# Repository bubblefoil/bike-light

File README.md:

# Cargo bike illumination

Cusomized bicycle RGB LED strip illumination controlled by Arduino UNO

# TODO
## Rezimy
- __Nocni:__ svitit vpredu max intenzitou (cca 6 LED z kraje), zbytek do konce nosice prichciple. To same v cervene vzadu.
- __Denni:__ To same co nocni, akorat ty prichciple nesviti vubec (stejne by to nebylo videt)
- __Parkovacky:__ sviti to prichciple cele, pricemz by bylo hezke umet menit intenzitu.
- __Blinkry:__ Max intenzivne oranzove z kraje prvnich cca 12LED prerusovane (oranzova/zhasnuto) a zbytek pri dennim nic a nocnim prichciple (bila ^ cervena)

## Rezimy 2.0

- __OFF:__ Vse 0%. Nejaka indikace?
- __Auto:__
  - Stred: 100%
  - Strany: Podle senzoru. Viz tabulka niz. Moznost menit citlivost stejne jako nastaveni jasu, tj. drzenim prepinace rezimu. Melo by stacit posouvat hranici sero/svetlo, kdy se strany vypinaji.
- __Manual:__
  - Vse podle hodnoty nastavene drzenim prepinace rezimu: 0-100%
  - 0-50%
    - Stred: 10-100%
    - Strany: Vypnute
  - 50-100%
    - Stred: 100%
    - Strany: 0-100%
- __Parking:__
  - Jas podle hodnoty nastavene drzenim prepinace rezimu: 0-100%
  - Vse sviti stejne
- __Usporny rezim:__
  - Jas podle hodnoty nastavene drzenim prepinace rezimu: 0-100%
  - Stred: Blikani (plynule pulzovani? Animace jednotlivych LED?)
  - Strany: Vypnute
  - Zmensit jas/sirku blinkru?

| Senzor    | Jas [%] |
| --------- | ------- |
| Tma       | ~1      |
| Sero      | ~25     |
| Svetlo    | 0       |

> To by bylo v prvni verzi vsechno. Couvacky, signalizace zamykani, kradeni, svetelna houkacka, vykreslovani bassu hudby apod.nechame na pozdeji ;)

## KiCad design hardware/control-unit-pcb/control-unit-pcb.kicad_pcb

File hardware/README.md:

# Controller HW diagram

The cargo bike is already equiped with its own 12V battery.

Controller is programmed to work with 3 switches. A couple for turn signals and one with press/hold functions to switch light modes and control brightness.
There are [motorcycle switches like this](https://www.banggood.com/22mm-Handlebar-Light-Horn-OnOff-Signal-Indicator-Switch-For-Motorcycle-E-bike-p-1211467.html) available on the market.

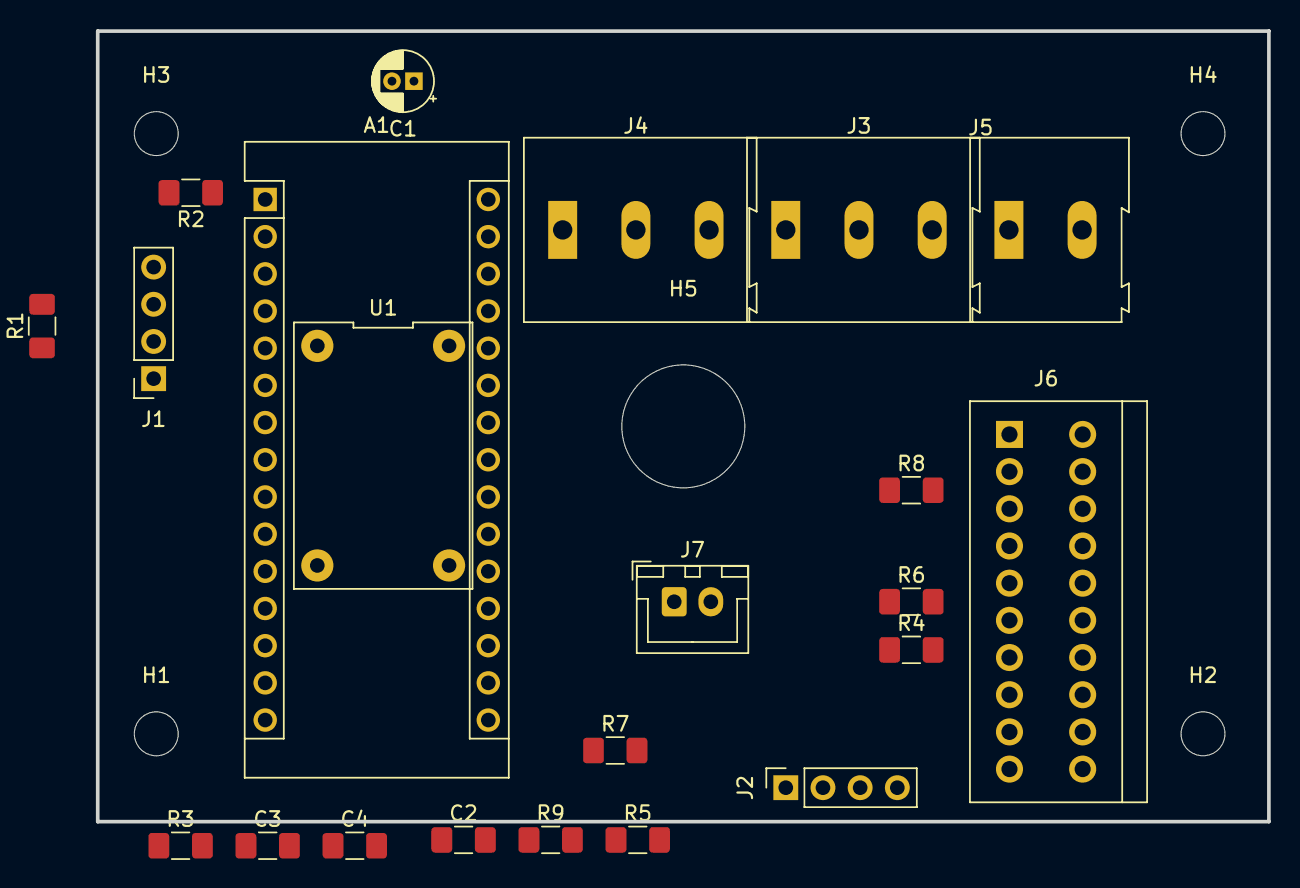
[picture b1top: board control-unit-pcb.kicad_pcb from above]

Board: 2 copper layers, 80.0 x 54.0 mm, 27 parts (0 on the bottom side), 15 nets, no tracks yet.

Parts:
A1: Arduino_Nano_v3.x; Arduino_Nano
C1: 1uF; CP_Radial_D4.0mm_P1.50mm
C2, C3, C4: 100nF; C_1206_3216Metric_Pad1.42x1.75mm_HandSolder
H1, H2, H3, H4: MountingHole; MountingHole_3mm
H5: MountingHole; MountingHole_8.4mm_M8
J1, J2: Conn_01x04_Male; PinSocket_1x04_P2.54mm_Vertical
J3, J4: Screw_Terminal_01x03; TerminalBlock_Altech_AK300-3_P5.00mm
J5: Screw_Terminal_01x02; TerminalBlock_Altech_AK300-2_P5.00mm
J6: Conn_02x10_Row_Letter_Last; TerminalBlock_PTR_AKZ3191_10KD-2x10_2.54x5.00
J7: Conn_01x02_Male; JST_XH_B2B-XH-A_1x02_P2.50mm_Vertical
R1: 2k2; R_1206_3216Metric_Pad1.42x1.75mm_HandSolder
R2: 1k2; R_1206_3216Metric_Pad1.42x1.75mm_HandSolder
R3, R4, R5, R6, R7: R; R_1206_3216Metric_Pad1.42x1.75mm_HandSolder
R8: 2M; R_1206_3216Metric_Pad1.42x1.75mm_HandSolder
R9: 10M; R_1206_3216Metric_Pad1.42x1.75mm_HandSolder
U1: MP2307; MP2037

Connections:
+5V: A1.27, J1.1, J7.2
+7.5V: A1.30, C1.1, C2.2
GND: A1.4, A1.29, C1.2, C2.1, C3.2, C4.2, J1.2, J2.4, J3.1, J4.3, J5.1, R1.1, R7.1, R8.1
LED_FL: J4.1, R6.2
LED_FR: J3.3, R5.2
unnamed: A1.1, R2.1
unnamed: A1.5, R3.1
unnamed: A1.6, R4.1
unnamed: A1.7, R5.1
unnamed: A1.8, R6.1
unnamed: A1.19, C3.1, J7.1, R7.2
unnamed: A1.20, C4.1, R8.2, R9.2
RX: A1.2, J1.3
TX: J1.4, R1.2, R2.2
VCC: J2.1, J3.2, J4.2, J5.2

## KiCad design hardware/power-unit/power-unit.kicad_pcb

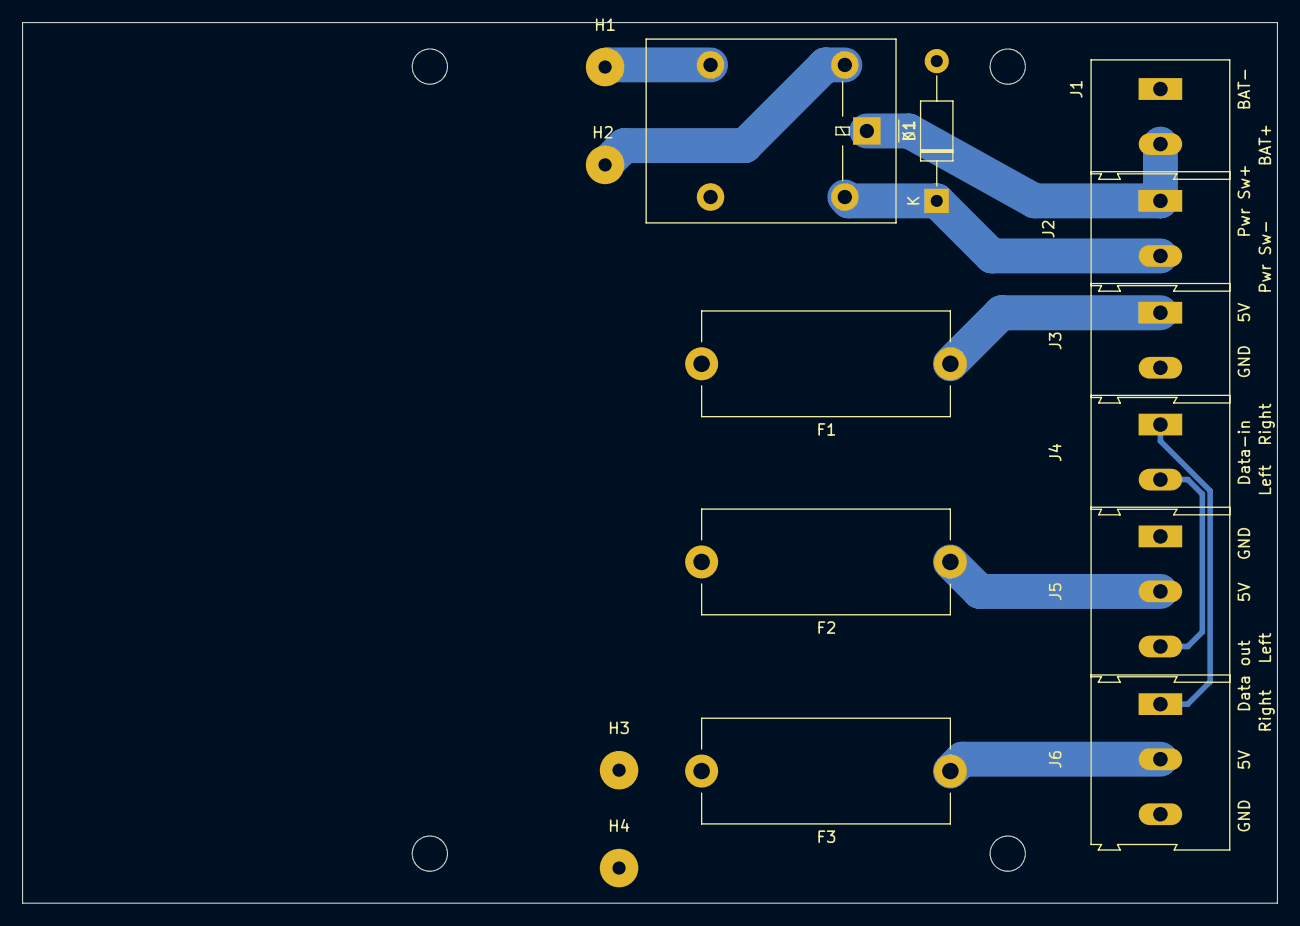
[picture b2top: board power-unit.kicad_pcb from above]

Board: 2 copper layers, 114.0 x 80.0 mm, 19 parts (0 on the bottom side), 11 nets.

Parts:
D1: D; D_DO-41_SOD81_P12.70mm_Horizontal
F1: 5A; Fuseholder_Cylinder-5x20mm_Stelvio-Kontek_PTF78_Horizontal_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
F2, F3: 2.5A; Fuseholder_Cylinder-5x20mm_Stelvio-Kontek_PTF78_Horizontal_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
H1: VCC; SolderWirePad_1x01_Drill1.2mm
H2, H4: GND; SolderWirePad_1x01_Drill1.2mm
H3: +5V; SolderWirePad_1x01_Drill1.2mm
H5, H6, H7, H8: MountingHole; MountingHole_3.2mm_M3
J1: VCC 12V; TerminalBlock_Altech_AK300-2_P5.00mm
J2: PWR Switch; TerminalBlock_Altech_AK300-2_P5.00mm
J3: 5V out; TerminalBlock_Altech_AK300-2_P5.00mm
J4: Rear LED data; TerminalBlock_Altech_AK300-2_P5.00mm
J5: LED left; TerminalBlock_Altech_AK300-3_P5.00mm
J6: LED right; TerminalBlock_Altech_AK300-3_P5.00mm
K1: G5LE-1; Relay_SPDT_Omron-G5LE-1

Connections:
+5V: F1.2, F2.2, F3.2, H3.1
BAT+: J1.2, J2.1, K1.1
GND: H4.1, J3.2, J5.1, J6.3
GNDPWR: D1.2, H2.1, J1.1, K1.2
unnamed: F1.1, J3.1
unnamed: F2.1, J5.2
unnamed: F3.1, J6.2
unnamed: H1.1, K1.3
unnamed: J4.1, J6.1
unnamed: J4.2, J5.3
PRWSW: D1.1, J2.2, K1.5

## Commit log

2019-05-18 Basic light modes
2019-05-18 Add basic blinkers
2019-05-18 Add circuit image
2019-05-19 Add wiring image
2019-05-22 Add brightness control
2019-05-22 Simplified blinkers with a button lib. Add ambient light reading.
2019-05-22 Updated modes in readme
2019-05-29 Split LED strip into 4 pieces and rewired
2019-05-29 Add OOP light modes
2019-06-19 Add package diagram
2019-06-19 Add HW diagram
2019-06-22 Add Brightness change function for manual mode
2020-02-04 Added LED Strip HW Schema.svg
2020-02-04 Rename LED Strip HW Schema.svg to controller-schema.svg
2020-02-18 Update pinout
2020-02-20 control-unit-hw-schema.drawio
2020-02-20 Rename Untitled Diagram.drawio to control-unit-hw-schema.drawio
2020-02-21 Back to pullup, fix BT pinout
2020-02-21 Attempt to read commands from Serial
2020-02-21 Add TODO list
2020-02-24 Project ported to PlatformIO
2020-02-25 Added power-unit.drawio
2020-02-25 Import power-unit.drawio content
2020-02-25 Add crude pcb layout
2020-03-11 Add KiCad project for power unit
2020-03-11 Update hw schematics
2020-03-23 Update power unit pcb
2020-03-23 Add control unit kicad schema
2020-03-23 Ignore kicad autosave files
2020-05-02 Assign some footprints
2020-05-02 Add powering issue note
2020-05-02 Battery voltage prep
2020-06-21 HW Schema update
2020-06-21 Ctrl unit kicad - separate mcu voltage regulator
2020-07-09 Improve light modes
2020-07-09 Update ctrl module schema
2020-07-09 Battery measurement
2020-07-12 Hazard lights by gesture
2020-07-12 Power-saving mode and hazard lights
2020-07-13 Power saving mode and animated blinkers
